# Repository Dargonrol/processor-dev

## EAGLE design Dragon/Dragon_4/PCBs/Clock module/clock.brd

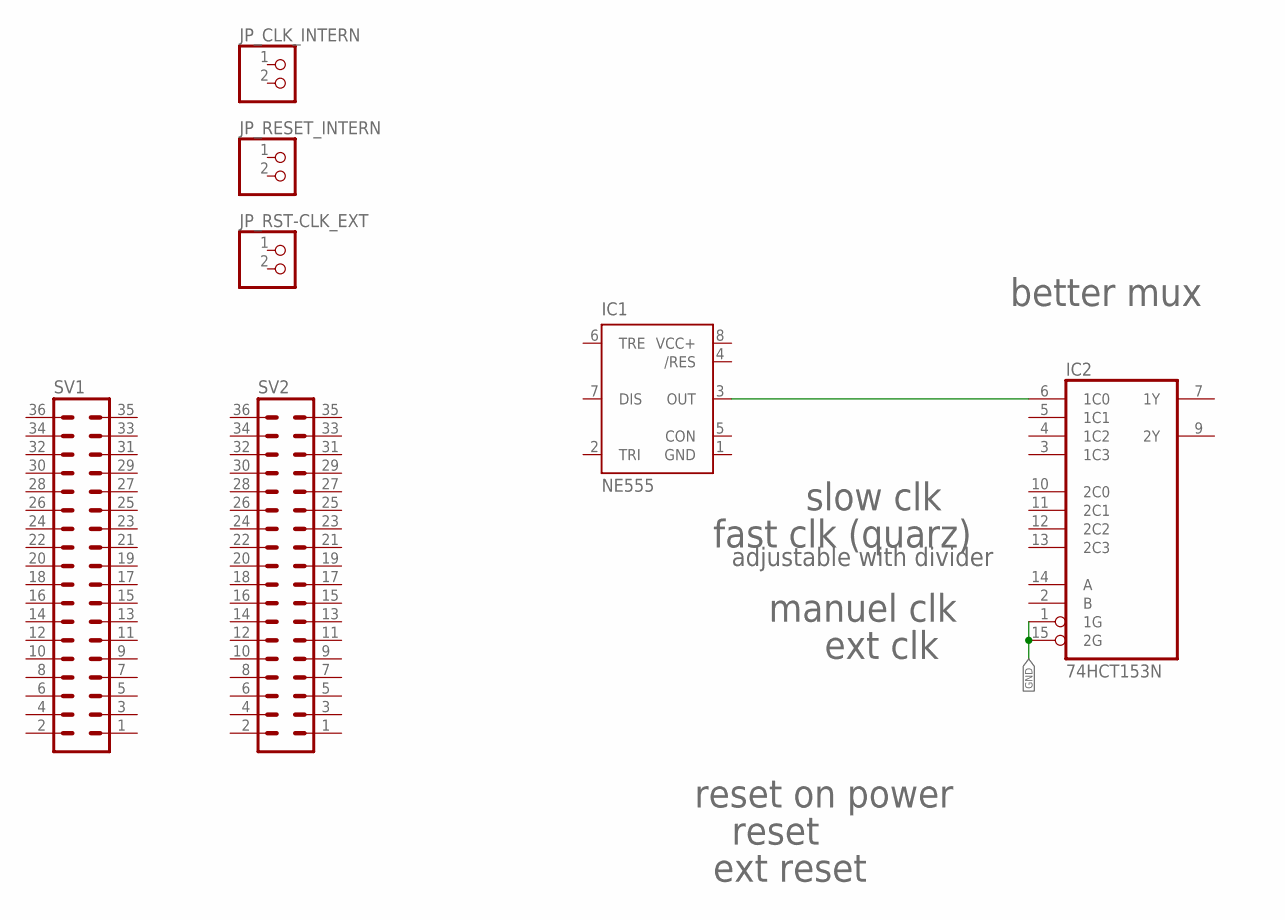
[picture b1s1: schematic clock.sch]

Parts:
IC1: NE555; DIL-08
IC2: 74HCT153N; DIL16
JP_CLK_INTERN: PINHD-1X2; 1X02
JP_RESET_INTERN: PINHD-1X2; 1X02
JP_RST-CLK_EXT: PINHD-1X2; 1X02
SV1, SV2: MA18-2

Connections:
GND: IC1.1 (GND), IC2.1 (1G), IC2.8 (GND), IC2.15 (2G)
unnamed: IC1.3 (OUT), IC2.6 (1C0)
VCC: IC2.16 (VCC)
VCC+: IC1.8 (VCC+)

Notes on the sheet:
better mux
slow clk
fast clk (quarz)
adjustable with divider
manuel clk
ext clk
reset on power
reset
ext reset

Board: 2 copper layers, 7 parts (0 on the bottom side), 2 nets, no tracks yet.

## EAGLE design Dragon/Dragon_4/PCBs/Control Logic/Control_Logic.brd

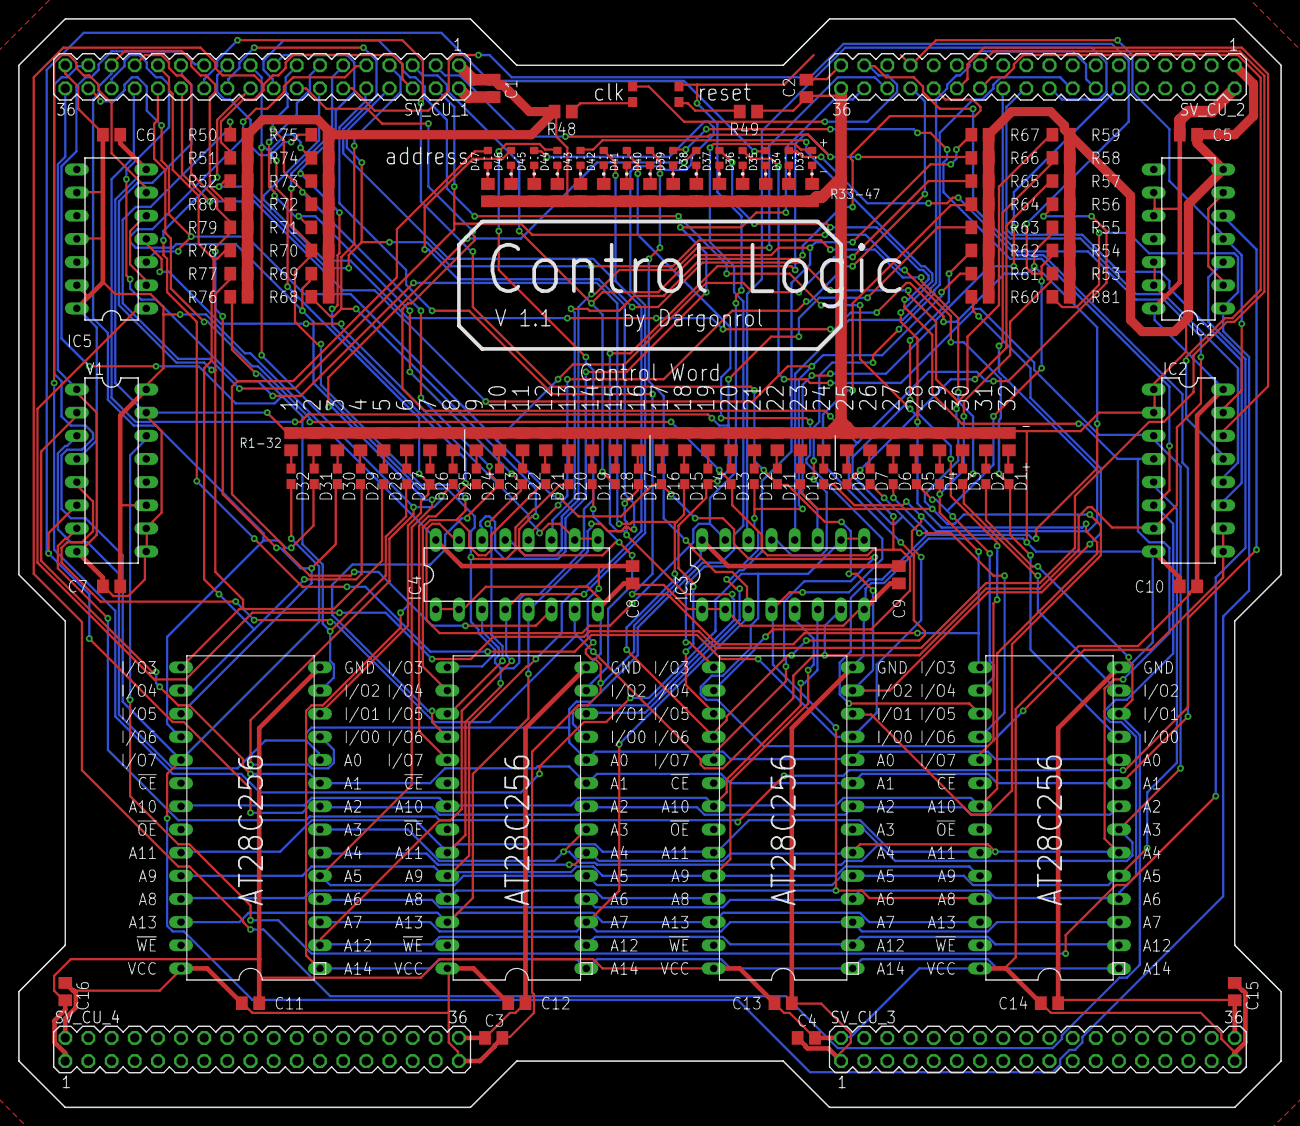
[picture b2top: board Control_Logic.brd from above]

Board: 2 copper layers, 138.4 x 119.4 mm, 160 parts (0 on the bottom side), 119 nets.

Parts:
C1, C2, C3, C4, C5, C6, C7, C8, C9, C10, C11, C12, C13, C14, C15, C16: C0805
CLK_LED: LTST-C193TBKT-5A; 0603
D1, D2, D3, D4, D5, D6, D7, D8, D9, D10, D11, D12, D13, D14, D15, D16, D17, D18, D19, D20, D21, D22, D23, D24, D25, D26, D27, D28, D29, D30, D31, D32: LTST-C193TBKT-5A; 0603
D33, D34, D35, D36, D37, D38, D39, D40, D41, D42, D43, D44, D45, D46, D47: LTST-C193KRKT-5A; LEDC1608X45N
IC1: 74HCT32N; DIL14
IC2, IC3, IC4: 74HCT173N; DIL16
IC5: 74HCT04N; DIL14
R1, R2, R3, R4, R5, R6, R7, R8, R9, R10, R11, R12, R13, R14, R15, R16, R17, R18, R19, R20, R21, R22, R23, R24, R25, R26, R27, R28, R29, R30, R31, R32, R33, R34, R35, R36, R37, R38, R39, R40, R41, R42, R43, R44, R45, R46, R47, R48, R49, R50, R51, R52, R53, R54, R55, R56, R57, R58, R59, R60, R61, R62, R63, R64, R65, R66, R67, R68, R69, R70, R71, R72, R73, R74, R75, R76, R77, R78, R79, R80, R81: R0805
RESET_LED: LTST-C193TBKT-5A; 0603
SV_CU_1, SV_CU_2, SV_CU_3, SV_CU_4: MA18-2
U$1, U$2, U$3, U$4: AT28C256
V1: 74193N; DIL16

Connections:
BUS_CLK: CLK_LED.2, IC2.7, IC3.7, IC4.7, SV_CU_2.33, V1.5
BUS_CTRL1_REG_A_1: D1.2, R50.1, SV_CU_1.4, U$1.I/O0
BUS_CTRL2_REG_A_2: D2.2, R51.1, SV_CU_1.6, U$1.I/O1
BUS_CTRL3_REG_A_3: D3.2, R52.1, SV_CU_1.8, U$1.I/O2
BUS_CTRL4_REG_A_4: D4.2, R53.1, SV_CU_1.10, U$1.I/O3
BUS_CTRL5_REG_L_1: D5.2, R54.1, SV_CU_1.12, U$1.I/O4
BUS_CTRL6_REG_L_2: D6.2, R55.1, SV_CU_1.14, U$1.I/O5
BUS_CTRL7_REG_L_3: D7.2, R56.1, SV_CU_1.16, U$1.I/O6
BUS_CTRL8_REG_L_4: D8.2, R57.1, SV_CU_1.18, U$1.I/O7
BUS_CTRL9_16REG_A_ADDR_1: D9.2, R58.1, SV_CU_1.20, U$2.I/O0
BUS_CTRL10_16REG_A_ADDR_2: D10.2, R59.1, SV_CU_1.22, U$2.I/O1
BUS_CTRL11_16REG_A_ADDR_3: D11.2, R60.1, SV_CU_1.24, U$2.I/O2
BUS_CTRL12_CREG_INC_1: D12.2, R61.1, SV_CU_1.26, U$2.I/O3
BUS_CTRL13_CREG_INC_2: D13.2, R62.1, SV_CU_1.28, U$2.I/O4
BUS_CTRL14_CREG_DEC_1: D14.2, R63.1, SV_CU_1.30, U$2.I/O5
BUS_CTRL15_CREG_DEC_2: D15.2, R64.1, SV_CU_1.32, U$2.I/O6
BUS_CTRL16_FLAGS: D16.2, IC5.3, R65.1, SV_CU_1.34, U$2.I/O7
BUS_CTRL17_GPR_A_ALU_R_1: D17.2, R66.1, SV_CU_1.3, U$3.I/O0
BUS_CTRL18_GPR_A_ALU_R_2: D18.2, R67.1, SV_CU_1.5, U$3.I/O1
BUS_CTRL19_GPR_A_ALU_R_3: D19.2, R68.1, SV_CU_1.7, U$3.I/O2
BUS_CTRL20_GPR_A_ALU_L_1: D20.2, R69.1, SV_CU_1.9, U$3.I/O3
BUS_CTRL21_GPR_A_ALU_L_2: D21.2, R70.1, SV_CU_1.11, U$3.I/O4
BUS_CTRL22_GPR_A_ALU_L_3: D22.2, R71.1, SV_CU_1.13, U$3.I/O5
BUS_CTRL23_NONE_1: D23.2, R72.1, SV_CU_1.15, U$3.I/O6
BUS_CTRL24_NONE_2: D24.2, R73.1, SV_CU_1.17, U$3.I/O7
BUS_CTRL25_ALU_OP_1: D25.2, R74.1, SV_CU_1.19, U$4.I/O0
BUS_CTRL26_ALU_OP_2: D26.2, R75.1, SV_CU_1.21, U$4.I/O1
BUS_CTRL27_ALU_OP_3: D27.2, R76.1, SV_CU_1.23, U$4.I/O2
BUS_CTRL28_ALU_OP_4: D28.2, R77.1, SV_CU_1.25, U$4.I/O3
BUS_CTRL29_DPLY_RS: D29.2, R78.1, SV_CU_1.27, U$4.I/O4
BUS_CTRL30_DPLY_RW: D30.2, R79.1, SV_CU_1.29, U$4.I/O5
BUS_CTRL31_HLT: D31.2, R80.1, SV_CU_1.31, U$4.I/O6
BUS_CTRL32_RST_STEP: D32.2, IC1.1, R81.1, SV_CU_1.33, U$4.I/O7
BUS_CTRL_IR_LOAD: IC5.1, SV_CU_2.23
BUS_FLAG_1: IC4.14, SV_CU_2.34
BUS_FLAG_2: IC4.13, SV_CU_2.32
BUS_FLAG_3: IC4.12, SV_CU_2.30
BUS_FLAG_4: IC4.11, SV_CU_2.28
BUS_MEMORY_BUS_0: IC2.14, SV_CU_2.26
BUS_MEMORY_BUS_1: IC2.13, SV_CU_2.24
BUS_MEMORY_BUS_2: IC2.12, SV_CU_2.22
BUS_MEMORY_BUS_3: IC2.11, SV_CU_2.20
BUS_MEMORY_BUS_4: IC3.14, SV_CU_2.18
BUS_MEMORY_BUS_5: IC3.13, SV_CU_2.16
BUS_MEMORY_BUS_6: IC3.12, SV_CU_2.14
BUS_MEMORY_BUS_7: IC3.11, SV_CU_2.12
BUS_RESET: IC1.4, IC2.15, IC3.15, IC4.15, RESET_LED.2, SV_CU_2.29
FLAG_1: D44.A, IC4.3, U$1.A11, U$2.A11, U$3.A11, U$4.A11
FLAG_2: D45.A, IC4.4, U$1.A12, U$2.A12, U$3.A12, U$4.A12
FLAG_3: D46.A, IC4.5, U$1.A13, U$2.A13, U$3.A13, U$4.A13
FLAG_4: D47.A, IC4.6, U$1.A14, U$2.A14, U$3.A14, U$4.A14
GND: C1.2, C2.2, C3.2, C4.2, C5.2, C6.2, C7.2, C8.2, C9.2, C10.2, C11.2, C12.2, C13.2, C14.2, C15.2, C16.2, IC1.7, IC2.1, IC2.2, IC2.8, IC3.1, IC3.2, IC3.8, IC4.1, IC4.2, IC4.8, IC5.7, R1.1, R2.1, R3.1, R4.1, R5.1, R6.1, R7.1, R8.1, R9.1, R10.1, R11.1, R12.1, R13.1, R14.1, R15.1, R16.1, R17.1, R18.1, R19.1, R20.1, R21.1, R22.1, R23.1, R24.1, R25.1, R26.1, R27.1, R28.1, R29.1, R30.1, R31.1, R32.1, R33.2, R34.2, R35.2, R36.2, R37.2, R38.2, R39.2, R40.2, R41.2, R42.2, R43.2, R44.2, R45.2, R46.2, R47.2, R48.1, R49.1, R50.2, R51.2, R52.2, R53.2, R54.2, R55.2, R56.2, R57.2, R58.2, R59.2, R60.2, R61.2, R62.2, R63.2, R64.2, R65.2, R66.2, R67.2, R68.2, R69.2, R70.2, R71.2, R72.2, R73.2, R74.2, R75.2, R76.2, R77.2, R78.2, R79.2, R80.2, R81.2, SV_CU_1.1, SV_CU_1.36, SV_CU_2.1, SV_CU_2.36, SV_CU_3.1, SV_CU_3.36, SV_CU_4.1, SV_CU_4.36, U$1.GND, U$2.GND, U$3.GND, U$4.GND, V1.1, V1.8, V1.9, V1.10, V1.15
unnamed: IC4.9, IC4.10, IC5.4
unnamed: IC2.9, IC2.10, IC3.9, IC3.10, IC5.6
unnamed: D1.1, R1.2
unnamed: D2.1, R2.2
unnamed: D3.1, R3.2
unnamed: D4.1, R4.2
unnamed: D5.1, R5.2
unnamed: D6.1, R6.2
unnamed: D7.1, R7.2
unnamed: D8.1, R8.2
unnamed: D9.1, R9.2
unnamed: D10.1, R10.2
unnamed: D11.1, R11.2
unnamed: D12.1, R12.2
unnamed: D13.1, R13.2
unnamed: D14.1, R14.2
unnamed: D15.1, R15.2
unnamed: D16.1, R16.2
unnamed: D17.1, R17.2
unnamed: D18.1, R18.2
unnamed: D19.1, R19.2
unnamed: D20.1, R20.2
unnamed: D21.1, R21.2
unnamed: D22.1, R22.2
unnamed: D23.1, R23.2
unnamed: D24.1, R24.2
unnamed: D25.1, R25.2
unnamed: D26.1, R26.2
unnamed: D27.1, R27.2
unnamed: D28.1, R28.2
unnamed: D29.1, R29.2
unnamed: D30.1, R30.2
unnamed: D31.1, R31.2
unnamed: D32.1, R32.2
unnamed: D33.C, R33.1
unnamed: D34.C, R34.1
unnamed: D35.C, R35.1
unnamed: D36.C, R36.1
unnamed: D37.C, R37.1
unnamed: D38.C, R38.1
unnamed: D39.C, R39.1
unnamed: D40.C, R40.1
unnamed: D41.C, R41.1
unnamed: D42.C, R42.1
unnamed: D43.C, R43.1
unnamed: D44.C, R44.1
unnamed: D45.C, R45.1
unnamed: D46.C, R46.1
unnamed: IC1.5, V1.7
unnamed: D47.C, R47.1
unnamed: CLK_LED.1, R48.2
unnamed: IC1.3, V1.14
unnamed: IC1.2, IC1.6
unnamed: R49.2, RESET_LED.1
unnamed: IC5.2, IC5.5
OP-CODE_1: D36.A, IC2.3, U$1.A3, U$2.A3, U$3.A3, U$4.A3
OP-CODE_2: D37.A, IC2.4, U$1.A4, U$2.A4, U$3.A4, U$4.A4
OP-CODE_3: D38.A, IC2.5, U$1.A5, U$2.A5, U$3.A5, U$4.A5
OP-CODE_4: D39.A, IC2.6, U$1.A6, U$2.A6, U$3.A6, U$4.A6
OP-CODE_5: D40.A, IC3.3, U$1.A7, U$2.A7, U$3.A7, U$4.A7
OP-CODE_6: D41.A, IC3.4, U$1.A8, U$2.A8, U$3.A8, U$4.A8
OP-CODE_7: D42.A, IC3.5, U$1.A9, U$2.A9, U$3.A9, U$4.A9
OP-CODE_8: D43.A, IC3.6, U$1.A10, U$2.A10, U$3.A10, U$4.A10
STEP_1: D33.A, U$1.A0, U$2.A0, U$3.A0, U$4.A0, V1.3
STEP_2: D34.A, U$1.A1, U$2.A1, U$3.A1, U$4.A1, V1.2
STEP_3: D35.A, U$1.A2, U$2.A2, U$3.A2, U$4.A2, V1.6
VCC: C1.1, C2.1, C3.1, C4.1, C5.1, C6.1, C7.1, C8.1, C9.1, C10.1, C11.1, C12.1, C13.1, C14.1, C15.1, C16.1, IC1.9, IC1.10, IC1.12, IC1.13, IC1.14, IC2.16, IC3.16, IC4.16, IC5.9, IC5.11, IC5.13, IC5.14, SV_CU_1.2, SV_CU_1.35, SV_CU_2.2, SV_CU_2.35, SV_CU_3.2, SV_CU_3.35, SV_CU_4.2, SV_CU_4.35, U$1.VCC, U$2.VCC, U$3.VCC, U$4.VCC, V1.4, V1.11, V1.16

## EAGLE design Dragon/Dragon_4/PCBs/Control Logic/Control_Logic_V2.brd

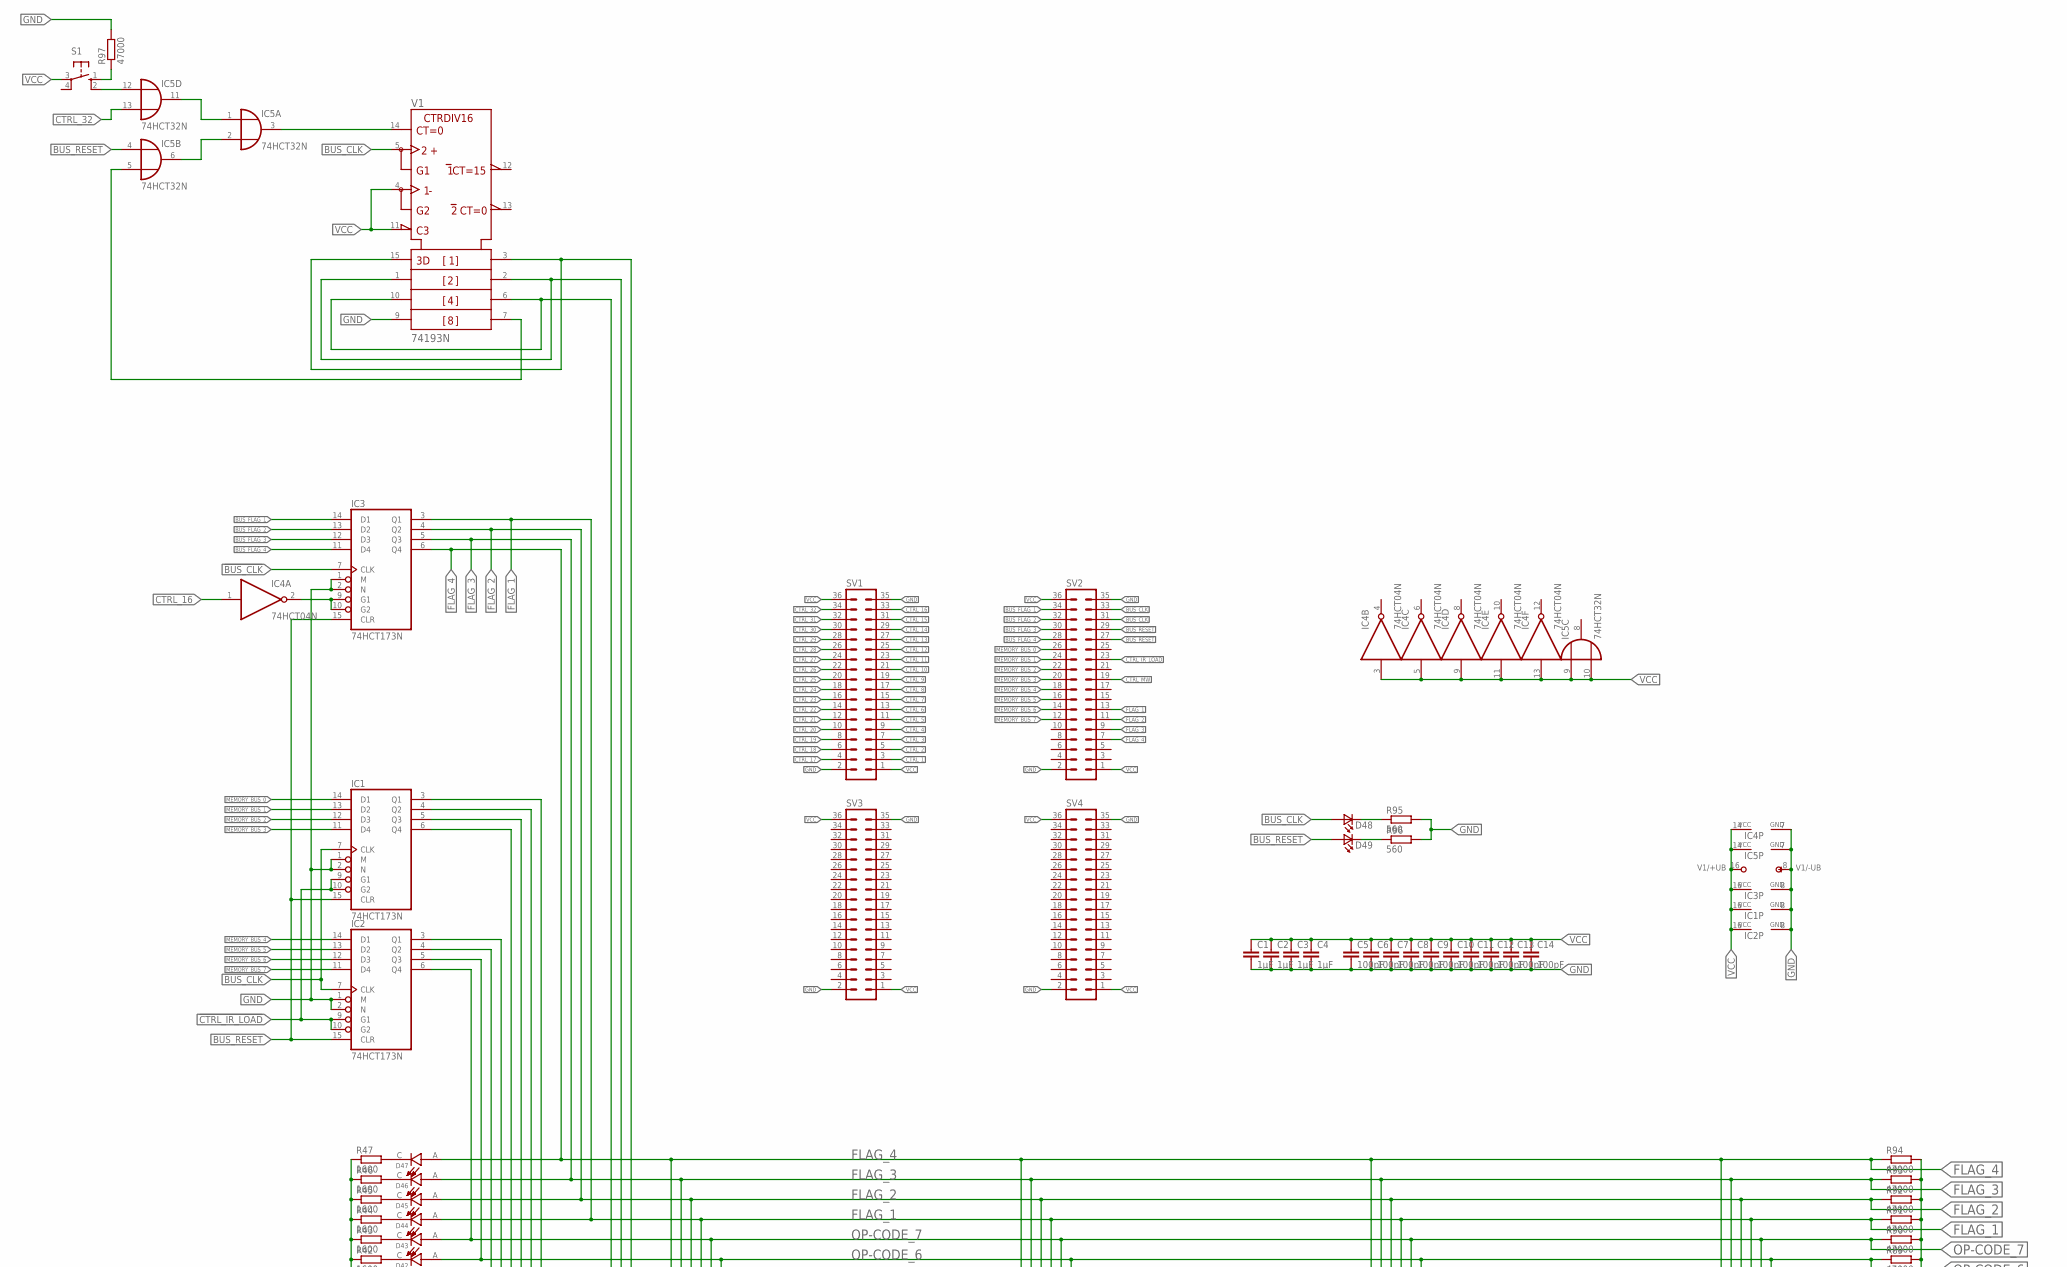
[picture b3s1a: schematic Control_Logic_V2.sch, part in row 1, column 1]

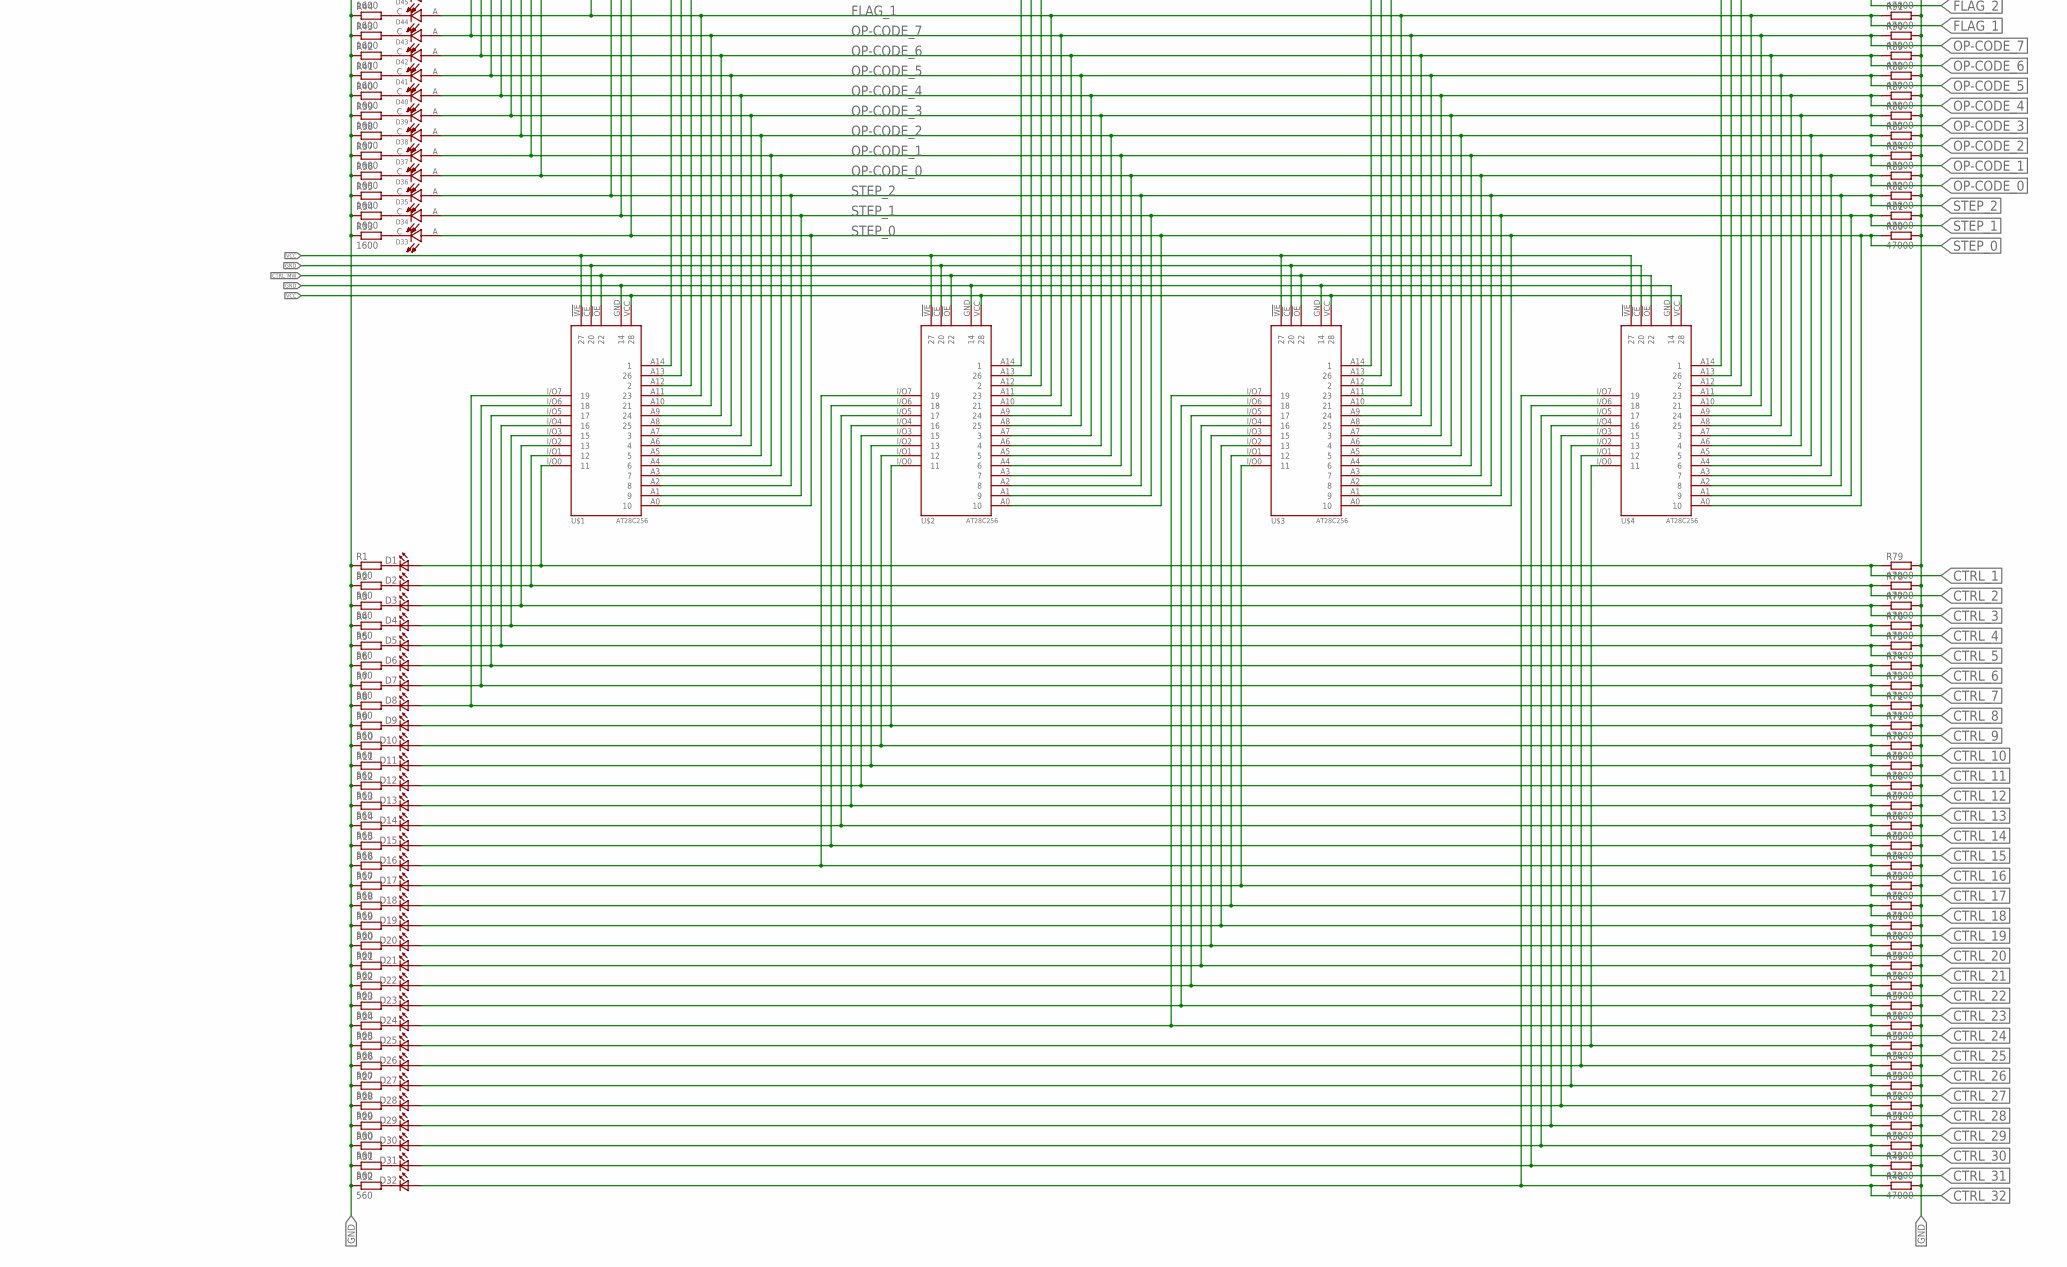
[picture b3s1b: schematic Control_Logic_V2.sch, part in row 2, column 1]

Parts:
C1, C2, C3, C4: 1µF; C0805
C5, C6, C7, C8, C9, C10, C11, C12, C13, C14: 100pF; C0805
D1, D2, D3, D4, D5, D6, D7, D8, D9, D10, D11, D12, D13, D14, D15, D16, D17, D18, D19, D20, D21, D22, D23, D24, D25, D26, D27, D28, D29, D30, D31, D32, D48, D49: LTST-C193TBKT-5A; 0603
D33, D34, D35, D36, D37, D38, D39, D40, D41, D42, D43, D44, D45, D46, D47: LTST-C193KRKT-5A; LEDC1608X45N
IC1, IC2, IC3: 74HCT173N; DIL16
IC4: 74HCT04N; DIL14
IC5: 74HCT32N; DIL14
R1, R2, R3, R4, R5, R6, R7, R8, R9, R10, R11, R12, R13, R14, R15, R16, R17, R18, R19, R20, R21, R22, R23, R24, R25, R26, R27, R28, R29, R30, R31, R32, R95, R96: 560; R0805
R33, R34, R35, R36, R37, R38, R39, R40, R41, R42, R43, R44, R45, R46, R47: 1600; R0805
R48, R49, R50, R51, R52, R53, R54, R55, R56, R57, R58, R59, R60, R61, R62, R63, R64, R65, R66, R67, R68, R69, R70, R71, R72, R73, R74, R75, R76, R77, R78, R79, R80, R81, R82, R83, R84, R85, R86, R87, R88, R89, R90, R91, R92, R93, R94, R97: 47000; R0805
S1: 10-XX; B3F-10XX
SV1, SV2, SV3, SV4: MA18-2
U$1, U$2, U$3, U$4: AT28C256
V1: 74193N; DIL16

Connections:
!BUS_CLK: IC3.7 (CLK), SV2.31
!BUS_RESET: SV2.27
!CTRL_IR_LOAD: IC1.9 (G1), IC1.10 (G2), IC2.9 (G1), IC2.10 (G2), SV2.23
BUS_CLK: D48.2 (A2), IC1.7 (CLK), IC2.7 (CLK), SV2.33, V1.5 (UP)
BUS_FLAG_1: IC3.14 (D1), SV2.34
BUS_FLAG_2: IC3.13 (D2), SV2.32
BUS_FLAG_3: IC3.12 (D3), SV2.30
BUS_FLAG_4: IC3.11 (D4), SV2.28
BUS_RESET: D49.2 (A2), IC1.15 (CLR), IC2.15 (CLR), IC3.15 (CLR), IC5.4 (I0), SV2.29
CTRL_1: D1.2 (A2), R79.1, SV1.3, U$1.I/O0 (11)
CTRL_2: D2.2 (A2), R78.1, SV1.5, U$1.I/O1 (12)
CTRL_3: D3.2 (A2), R77.1, SV1.7, U$1.I/O2 (13)
CTRL_4: D4.2 (A2), R76.1, SV1.9, U$1.I/O3 (15)
CTRL_5: D5.2 (A2), R75.1, SV1.11, U$1.I/O4 (16)
CTRL_6: D6.2 (A2), R74.1, SV1.13, U$1.I/O5 (17)
CTRL_7: D7.2 (A2), R73.1, SV1.15, U$1.I/O6 (18)
CTRL_8: D8.2 (A2), R72.1, SV1.17, U$1.I/O7 (19)
CTRL_9: D9.2 (A2), R71.1, SV1.19, U$2.I/O0 (11)
CTRL_10: D10.2 (A2), R70.1, SV1.21, U$2.I/O1 (12)
CTRL_11: D11.2 (A2), R69.1, SV1.23, U$2.I/O2 (13)
CTRL_12: D12.2 (A2), R68.1, SV1.25, U$2.I/O3 (15)
CTRL_13: D13.2 (A2), R67.1, SV1.27, U$2.I/O4 (16)
CTRL_14: D14.2 (A2), R66.1, SV1.29, U$2.I/O5 (17)
CTRL_15: D15.2 (A2), R65.1, SV1.31, U$2.I/O6 (18)
CTRL_16: D16.2 (A2), IC4.1 (I), R64.1, SV1.33, U$2.I/O7 (19)
CTRL_17: D17.2 (A2), R63.1, SV1.4, U$3.I/O0 (11)
CTRL_18: D18.2 (A2), R62.1, SV1.6, U$3.I/O1 (12)
CTRL_19: D19.2 (A2), R61.1, SV1.8, U$3.I/O2 (13)
CTRL_20: D20.2 (A2), R60.1, SV1.10, U$3.I/O3 (15)
CTRL_21: D21.2 (A2), R59.1, SV1.12, U$3.I/O4 (16)
CTRL_22: D22.2 (A2), R58.1, SV1.14, U$3.I/O5 (17)
CTRL_23: D23.2 (A2), R57.1, SV1.16, U$3.I/O6 (18)
CTRL_24: D24.2 (A2), R56.1, SV1.18, U$3.I/O7 (19)
CTRL_25: D25.2 (A2), R55.1, SV1.20, U$4.I/O0 (11)
CTRL_26: D26.2 (A2), R54.1, SV1.22, U$4.I/O1 (12)
CTRL_27: D27.2 (A2), R53.1, SV1.24, U$4.I/O2 (13)
CTRL_28: D28.2 (A2), R52.1, SV1.26, U$4.I/O3 (15)
CTRL_29: D29.2 (A2), R51.1, SV1.28, U$4.I/O4 (16)
CTRL_30: D30.2 (A2), R50.1, SV1.30, U$4.I/O5 (17)
CTRL_31: D31.2 (A2), R49.1, SV1.32, U$4.I/O6 (18)
CTRL_32: D32.2 (A2), IC5.13 (I1), R48.1, SV1.34, U$4.I/O7 (19)
CTRL_MW: SV2.19, U$1.!OE (22), U$2.!OE (22), U$3.!OE (22), U$4.!OE (22)
FLAG_1: D44.A, IC3.3 (Q1), R91.1, SV2.13, U$1.A11 (23), U$2.A11 (23), U$3.A11 (23), U$4.A11 (23)
FLAG_2: D45.A, IC3.4 (Q2), R92.1, SV2.11, U$1.A12 (2), U$2.A12 (2), U$3.A12 (2), U$4.A12 (2)
FLAG_3: D46.A, IC3.5 (Q3), R93.1, SV2.9, U$1.A13 (26), U$2.A13 (26), U$3.A13 (26), U$4.A13 (26)
FLAG_4: D47.A, IC3.6 (Q4), R94.1, SV2.7, U$1.A14 (1), U$2.A14 (1), U$3.A14 (1), U$4.A14 (1)
GND: C1.2, C2.2, C3.2, C4.2, C5.2, C6.2, C7.2, C8.2, C9.2, C10.2, C11.2, C12.2, C13.2, C14.2, IC1.1 (M), IC1.2 (N), IC1.8 (GND), IC2.1 (M), IC2.2 (N), IC2.8 (GND), IC3.1 (M), IC3.2 (N), IC3.8 (GND), IC4.7 (GND), IC5.7 (GND), R1.1, R2.1, R3.1, R4.1, R5.1, R6.1, R7.1, R8.1, R9.1, R10.1, R11.1, R12.1, R13.1, R14.1, R15.1, R16.1, R17.1, R18.1, R19.1, R20.1, R21.1, R22.1, R23.1, R24.1, R25.1, R26.1, R27.1, R28.1, R29.1, R30.1, R31.1, R32.1, R33.1, R34.1, R35.1, R36.1, R37.1, R38.1, R39.1, R40.1, R41.1, R42.1, R43.1, R44.1, R45.1, R46.1, R47.1, R48.2, R49.2, R50.2, R51.2, R52.2, R53.2, R54.2, R55.2, R56.2, R57.2, R58.2, R59.2, R60.2, R61.2, R62.2, R63.2, R64.2, R65.2, R66.2, R67.2, R68.2, R69.2, R70.2, R71.2, R72.2, R73.2, R74.2, R75.2, R76.2, R77.2, R78.2, R79.2, R80.2, R81.2, R82.2, R83.2, R84.2, R85.2, R86.2, R87.2, R88.2, R89.2, R90.2, R91.2, R92.2, R93.2, R94.2, R95.2, R96.2, R97.2, SV1.2, SV1.35, SV2.2, SV2.35, SV3.2, SV3.35, SV4.2, SV4.35, U$1.!CE (20), U$1.GND (14), U$2.!CE (20), U$2.GND (14), U$3.!CE (20), U$3.GND (14), U$4.!CE (20), U$4.GND (14), V1.8 (-UB), V1.9 (D)
MEMORY_BUS_0: IC1.14 (D1), SV2.26
MEMORY_BUS_1: IC1.13 (D2), SV2.24
MEMORY_BUS_2: IC1.12 (D3), SV2.22
MEMORY_BUS_3: IC1.11 (D4), SV2.20
MEMORY_BUS_4: IC2.14 (D1), SV2.18
MEMORY_BUS_5: IC2.13 (D2), SV2.16
MEMORY_BUS_6: IC2.12 (D3), SV2.14
MEMORY_BUS_7: IC2.11 (D4), SV2.12
unnamed: IC3.9 (G1), IC3.10 (G2), IC4.2 (O)
unnamed: IC5.1 (I0), IC5.11 (O)
unnamed: IC5.2 (I1), IC5.6 (O)
unnamed: IC5.3 (O), V1.14 (CLR)
unnamed: IC5.12 (I0), S1.2 (S1)
unnamed: R97.1, S1.1 (S)
unnamed: IC5.5 (I1), V1.7 (QD)
unnamed: D48.1 (K2), R95.1
unnamed: D49.1 (K2), R96.1
unnamed: D1.1 (K2), R1.2
unnamed: D2.1 (K2), R2.2
unnamed: D3.1 (K2), R3.2
unnamed: D4.1 (K2), R4.2
unnamed: D5.1 (K2), R5.2
unnamed: D6.1 (K2), R6.2
unnamed: D7.1 (K2), R7.2
unnamed: D8.1 (K2), R8.2
unnamed: D9.1 (K2), R9.2
unnamed: D10.1 (K2), R10.2
unnamed: D11.1 (K2), R11.2
unnamed: D12.1 (K2), R12.2
unnamed: D13.1 (K2), R13.2
unnamed: D14.1 (K2), R14.2
unnamed: D15.1 (K2), R15.2
unnamed: D16.1 (K2), R16.2
unnamed: D17.1 (K2), R17.2
unnamed: D18.1 (K2), R18.2
unnamed: D19.1 (K2), R19.2
unnamed: D20.1 (K2), R20.2
unnamed: D21.1 (K2), R21.2
unnamed: D22.1 (K2), R22.2
unnamed: D23.1 (K2), R23.2
unnamed: D24.1 (K2), R24.2
unnamed: D25.1 (K2), R25.2
unnamed: D26.1 (K2), R26.2
unnamed: D27.1 (K2), R27.2
unnamed: D28.1 (K2), R28.2
unnamed: D29.1 (K2), R29.2
unnamed: D30.1 (K2), R30.2
unnamed: D31.1 (K2), R31.2
unnamed: D32.1 (K2), R32.2
unnamed: D33.C, R33.2
unnamed: D34.C, R34.2
unnamed: D35.C, R35.2
unnamed: D36.C, R36.2
unnamed: D37.C, R37.2
unnamed: D38.C, R38.2
unnamed: D39.C, R39.2
unnamed: D40.C, R40.2
unnamed: D41.C, R41.2
unnamed: D42.C, R42.2
unnamed: D43.C, R43.2
unnamed: D44.C, R44.2
unnamed: D45.C, R45.2
unnamed: D46.C, R46.2
unnamed: D47.C, R47.2
OP-CODE_0: D36.A, IC1.3 (Q1), R83.1, U$1.A3 (7), U$2.A3 (7), U$3.A3 (7), U$4.A3 (7)
OP-CODE_1: D37.A, IC1.4 (Q2), R84.1, U$1.A4 (6), U$2.A4 (6), U$3.A4 (6), U$4.A4 (6)
OP-CODE_2: D38.A, IC1.5 (Q3), R85.1, U$1.A5 (5), U$2.A5 (5), U$3.A5 (5), U$4.A5 (5)
OP-CODE_3: D39.A, IC1.6 (Q4), R86.1, U$1.A6 (4), U$2.A6 (4), U$3.A6 (4), U$4.A6 (4)
OP-CODE_4: D40.A, IC2.3 (Q1), R87.1, U$1.A7 (3), U$2.A7 (3), U$3.A7 (3), U$4.A7 (3)
OP-CODE_5: D41.A, IC2.4 (Q2), R88.1, U$1.A8 (25), U$2.A8 (25), U$3.A8 (25), U$4.A8 (25)
OP-CODE_6: D42.A, IC2.5 (Q3), R89.1, U$1.A9 (24), U$2.A9 (24), U$3.A9 (24), U$4.A9 (24)
OP-CODE_7: D43.A, IC2.6 (Q4), R90.1, U$1.A10 (21), U$2.A10 (21), U$3.A10 (21), U$4.A10 (21)
STEP_0: D33.A, R80.1, U$1.A0 (10), U$2.A0 (10), U$3.A0 (10), U$4.A0 (10), V1.3 (QA), V1.15 (A)
STEP_1: D34.A, R81.1, U$1.A1 (9), U$2.A1 (9), U$3.A1 (9), U$4.A1 (9), V1.1 (B), V1.2 (QB)
STEP_2: D35.A, R82.1, U$1.A2 (8), U$2.A2 (8), U$3.A2 (8), U$4.A2 (8), V1.6 (QC), V1.10 (C)
VCC: C1.1, C2.1, C3.1, C4.1, C5.1, C6.1, C7.1, C8.1, C9.1, C10.1, C11.1, C12.1, C13.1, C14.1, IC1.16 (VCC), IC2.16 (VCC), IC3.16 (VCC), IC4.3 (I), IC4.5 (I), IC4.9 (I), IC4.11 (I), IC4.13 (I), IC4.14 (VCC), IC5.9 (I0), IC5.10 (I1), IC5.14 (VCC), S1.3, SV1.1, SV1.36, SV2.1, SV2.36, SV3.1, SV3.36, SV4.1, SV4.36, U$1.!WE (27), U$1.VCC (28), U$2.!WE (27), U$2.VCC (28), U$3.!WE (27), U$3.VCC (28), U$4.!WE (27), U$4.VCC (28), V1.4 (DOWN), V1.11 (!LOAD), V1.16 (+UB)

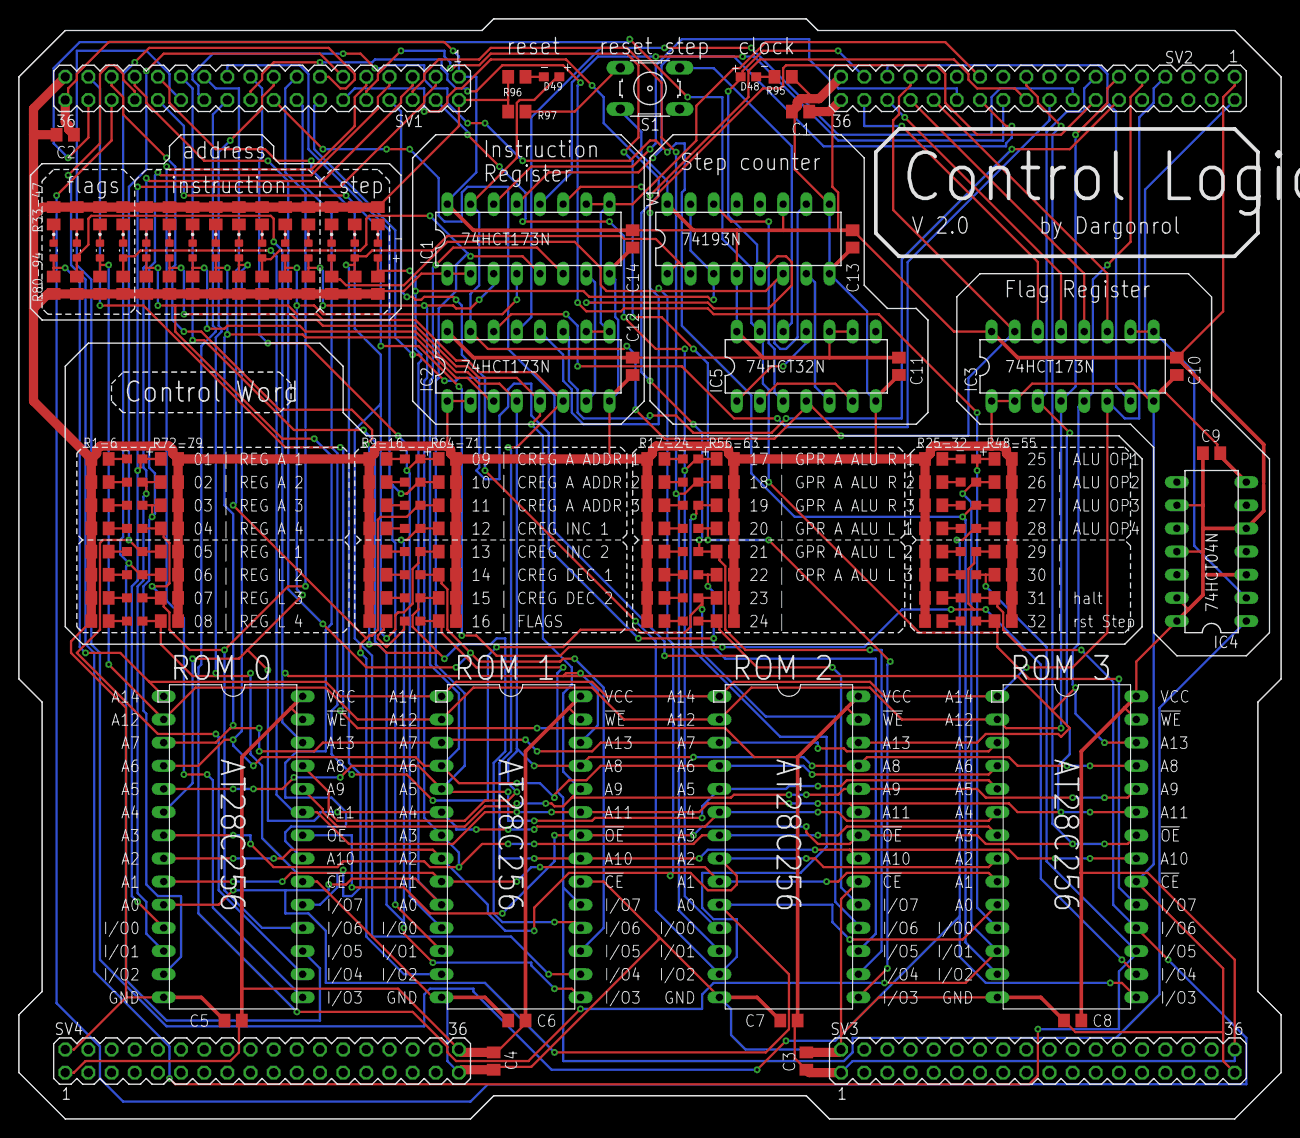
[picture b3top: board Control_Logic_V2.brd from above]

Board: 2 copper layers, 138.4 x 120.7 mm, 175 parts (0 on the bottom side), 122 nets.

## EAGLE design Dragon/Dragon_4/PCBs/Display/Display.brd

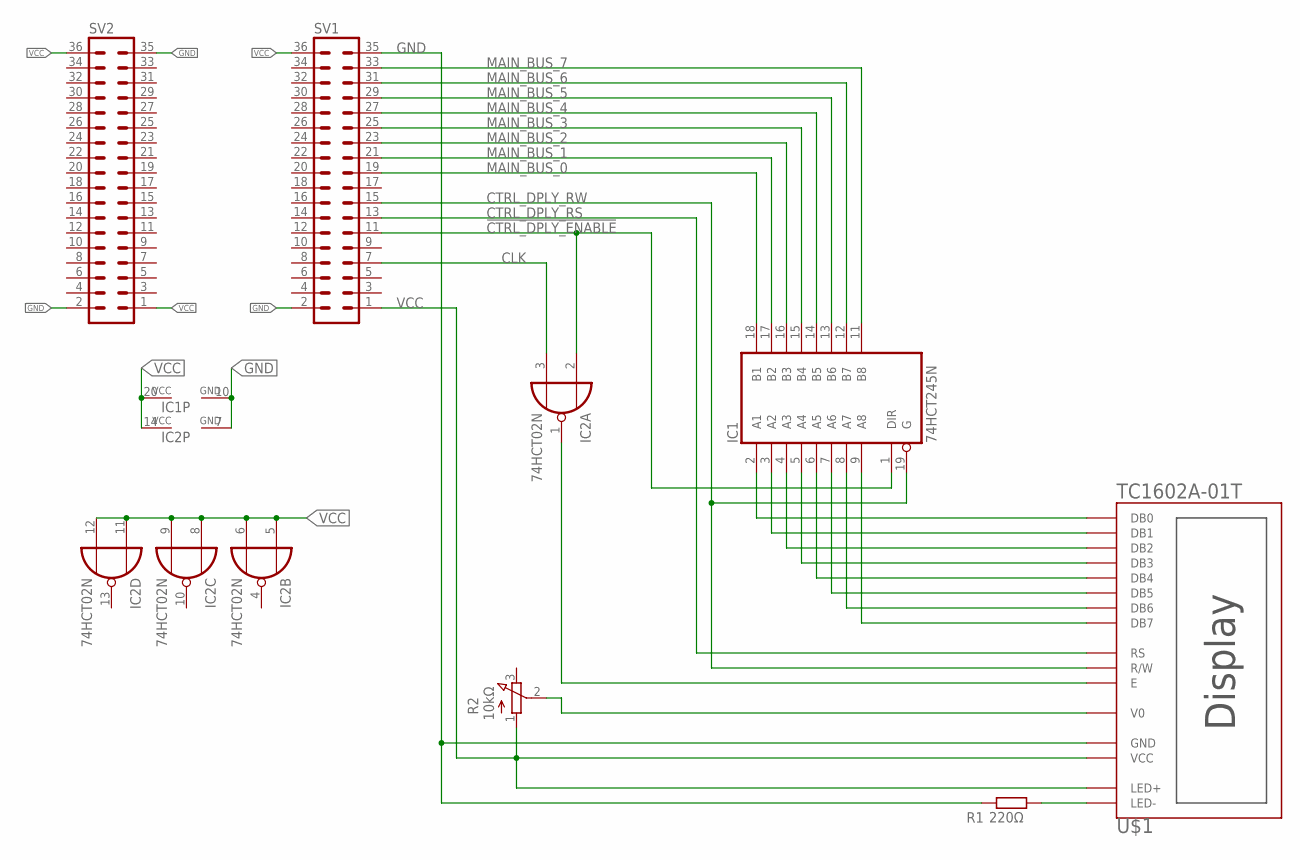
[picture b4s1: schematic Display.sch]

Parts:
IC1: 74HCT245N; DIL20
IC2: 74HCT02N; DIL14
R1: 220Ω; 0207/10
R2: 10kΩ; 3RP/1610N
SV1, SV2: MA18-2
U$1: TC1602A-01T

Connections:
!CTRL_DPLY_ENABLE: IC1.1 (DIR), IC2.2 (I0), SV1.11
CLK: IC2.3 (I1), SV1.7
CTRL_DPLY_RS: SV1.13, U$1.RS
CTRL_DPLY_RW: IC1.19 (G), SV1.15, U$1.R/W
GND: IC1.10 (GND), IC2.7 (GND), R1.1, SV1.2, SV1.35, SV2.2, SV2.35, U$1.GND
MAIN_BUS_0: IC1.18 (B1), SV1.19
MAIN_BUS_1: IC1.17 (B2), SV1.21
MAIN_BUS_2: IC1.16 (B3), SV1.23
MAIN_BUS_3: IC1.15 (B4), SV1.25
MAIN_BUS_4: IC1.14 (B5), SV1.27
MAIN_BUS_5: IC1.13 (B6), SV1.29
MAIN_BUS_6: IC1.12 (B7), SV1.31
MAIN_BUS_7: IC1.11 (B8), SV1.33
unnamed: R1.2, U$1.LED-
unnamed: R2.2 (S), U$1.V0
unnamed: IC1.9 (A8), U$1.DB7
unnamed: IC1.8 (A7), U$1.DB6
unnamed: IC1.7 (A6), U$1.DB5
unnamed: IC1.6 (A5), U$1.DB4
unnamed: IC1.5 (A4), U$1.DB3
unnamed: IC1.4 (A3), U$1.DB2
unnamed: IC1.3 (A2), U$1.DB1
unnamed: IC1.2 (A1), U$1.DB0
unnamed: IC2.1 (O), U$1.E
VCC: IC1.20 (VCC), IC2.5 (I0), IC2.6 (I1), IC2.8 (I0), IC2.9 (I1), IC2.11 (I0), IC2.12 (I1), IC2.14 (VCC), R2.1 (A), SV1.1, SV1.36, SV2.1, SV2.36, U$1.LED+, U$1.VCC

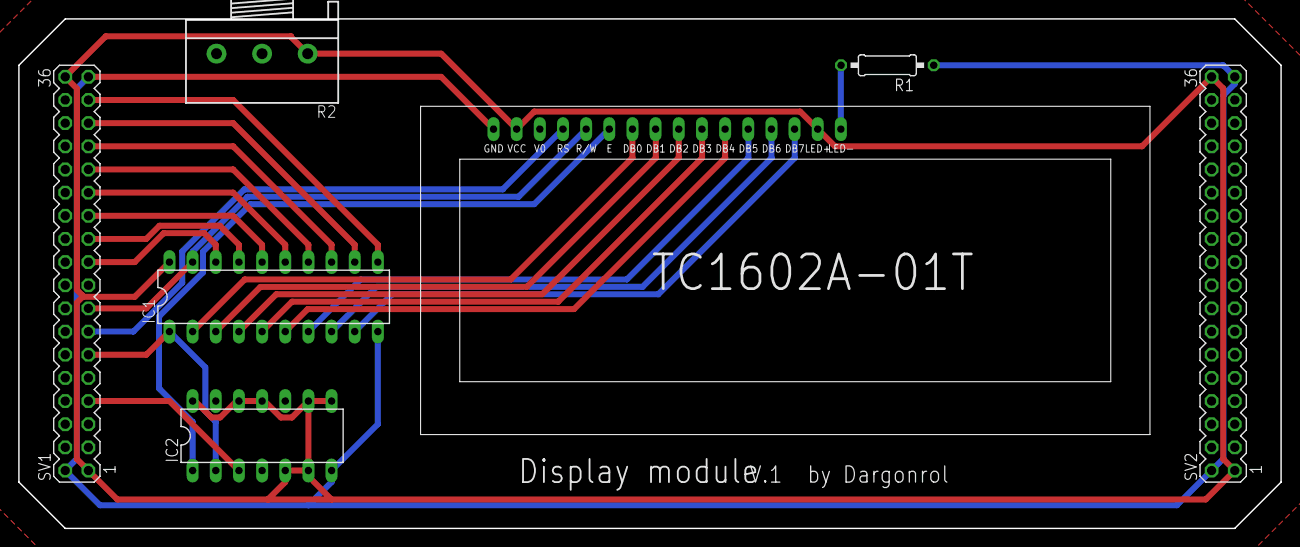
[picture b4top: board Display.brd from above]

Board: 2 copper layers, 138.4 x 55.9 mm, 7 parts (0 on the bottom side), 25 nets.
